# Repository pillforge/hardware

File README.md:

Development Hardware
====================

Schematic and PCB files for development hardware.

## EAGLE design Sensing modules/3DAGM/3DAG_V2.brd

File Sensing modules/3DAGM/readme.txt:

XXXXXXXXXXXXXXXXXXXXXXXXXXXXXXXXXXXXXXXXXXXXXXXXXXXXXXXXXXXXXXXXXXXXXXXXXXXXX
X                                                                           X
X   Artwork and documentation done by: STORM LAB                            X
X                                                                           X
X   Company: VANDERBILT UNIVERSITY                                          X
XXXXXXXXXXXXXXXXXXXXXXXXXXXXXXXXXXXXXXXXXXXXXXXXXXXXXXXXXXXXXXXXXXXXXXXXXXXXX

PROJECT : 3DAGM
PCB NAME : 3DAGM
REVISION: 1.1 
DATE: 4-28-2015

PCB DESCRIPTION: 2 LAYER PCB 0.8 MM NOMINAL THICKNESS FR4
		Dimensions in mil (0.001 inch)
                            DOUBLE SIDE SOLDER MASK,
                            DOUBLE SIDE SILKSCREEN,
                            6 MIL MIN TRACE WIDTH AND 6 MIL MIN ISOLATION
		Dielectric constant for FR4 is 4.5

FILE NAME            		DESCRIPTION                               	FILE TYPE
-------------------------------------------------------------------------------------------
***PCB MANUFACTURING FILES:
3DAGM.cmp				LAYER 1 COMPONENT SIDE/POSITIV              EXT. GERBER
3DAGM.sol				LAYER 2 Inner layer/POSITIV                 EXT. GERBER

3DAGM.stc				SOLDER MASK COMPONENT SIDE/NEGATIVE         EXT. GERBER
3DAGM.stl				SOLDER MASK SOLDER SIDE/NEGATIVE            EXT. GERBER

3DAGM.plc				SILKSCREEN COMPONENT SIDE/POSITIVE          EXT. GERBER
3DAGM.pls				SILKSCREEN SOLDER SIDE/POSITIVE             EXT. GERBER

3DAGM.crc				SOLDER PAST COMPONENT SIDE/POSITIVE         EXT. GERBER
3DAGM.crs				SOLDER PAST SOLDER SIDE/POSITIVE            EXT. GERBER

3DAGM.drd				DRILL/MECHANICAL DRAWING                    EXT. GERBER
3DAGM.dri				DRILL/NC DRILL REPORT                       ASCII
3DAGM.dim				BOARD OUTLINE             		    EXT. GERBER

3DAGM_partlist.xls		PART LIST					    ASCII

***PDF FILES:
3DAGM.PDF	Circuit Diagram

***EAGLE  FILES:
3DAGM.SCH			Eagle 6.6 Schematic file
3DAGM.BRD			Eagle 6.6 Layout file

README.TXT              THIS FILE                                   ASCII

***REVISION HISTORY

none

END.

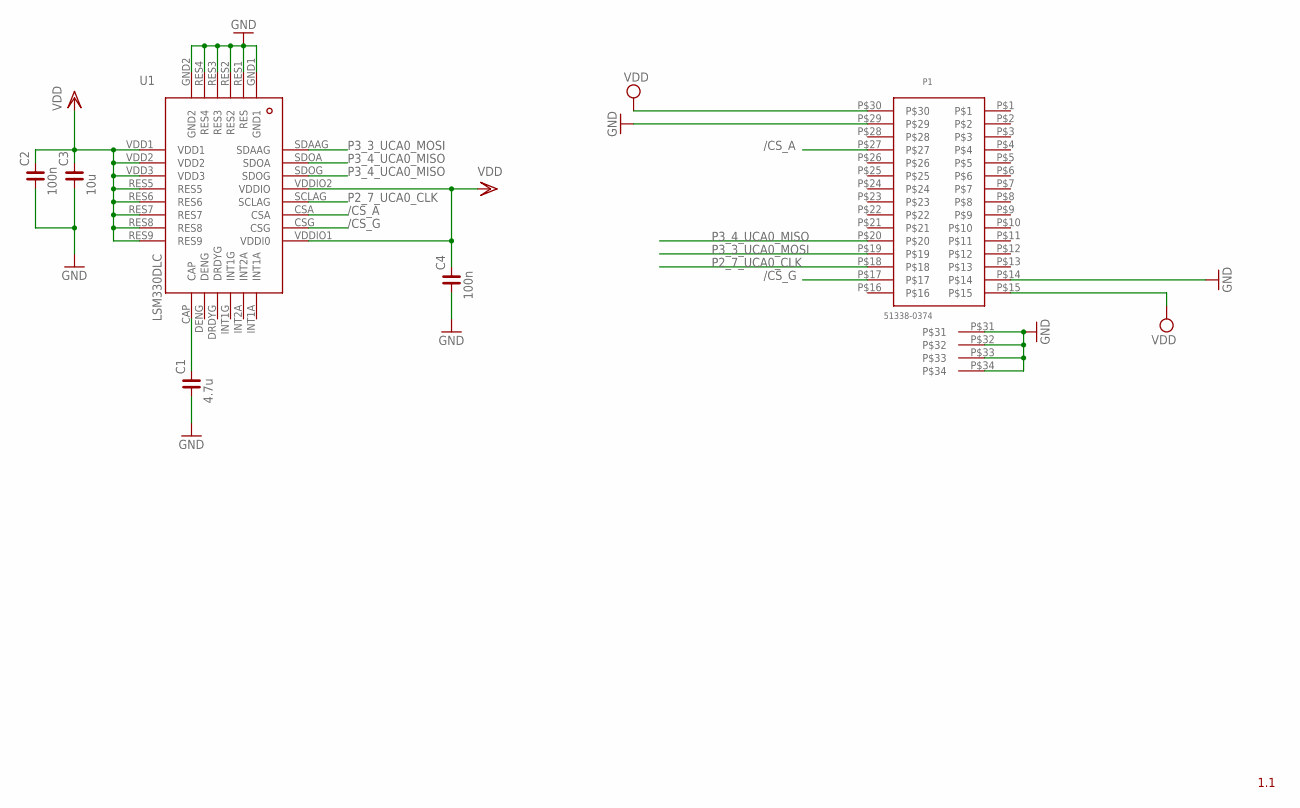
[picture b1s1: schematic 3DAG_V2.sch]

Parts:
C1: 4.7u; C0402
C2, C4: 100n; C0402
C3: 10u; C0402
P1: 51338-0374; 51338-0374_RECEPTACLE
U$4: LSM330DLC

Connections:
/CS_A: P1.P$27, U$4.CSA
/CS_G: P1.P$17, U$4.CSG
GND: C1.1, C2.1, C3.1, C4.1, P1.P$14, P1.P$29, P1.P$31, P1.P$32, P1.P$33, P1.P$34, U$4.GND1, U$4.GND2, U$4.RES1 (RES), U$4.RES2, U$4.RES3, U$4.RES4
unnamed: C1.2, U$4.CAP
P2_7_UCA0_CLK: P1.P$18, U$4.SCLAG
P3_3_UCA0_MOSI: P1.P$19, U$4.SDAAG
P3_4_UCA0_MISO: P1.P$20, U$4.SDOA, U$4.SDOG
VDD: C2.2, C3.2, C4.2, P1.P$15, P1.P$30, U$4.RES5, U$4.RES6, U$4.RES7, U$4.RES8, U$4.RES9, U$4.VDD1, U$4.VDD2, U$4.VDD3, U$4.VDDIO1 (VDDI0), U$4.VDDIO2 (VDDIO)

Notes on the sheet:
1.1

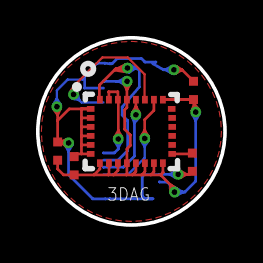
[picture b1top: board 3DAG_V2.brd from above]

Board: 2 copper layers, 10.4 x 10.4 mm, 6 parts (1 on the bottom side), 8 nets.

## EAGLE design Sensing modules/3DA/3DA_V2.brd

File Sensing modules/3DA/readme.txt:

XXXXXXXXXXXXXXXXXXXXXXXXXXXXXXXXXXXXXXXXXXXXXXXXXXXXXXXXXXXXXXXXXXXXXXXXXXXXX
X                                                                           X
X   Artwork and documentation done by: STORM LAB                            X
X                                                                           X
X   Company: VANDERBILT UNIVERSITY                                          X
XXXXXXXXXXXXXXXXXXXXXXXXXXXXXXXXXXXXXXXXXXXXXXXXXXXXXXXXXXXXXXXXXXXXXXXXXXXXX

PROJECT : 3da
PCB NAME : 3da
REVISION: 1.1 
DATE: 4-28-2015

PCB DESCRIPTION: 2 LAYER PCB 0.8 MM NOMINAL THICKNESS FR4
		Dimensions in mil (0.001 inch)
                            DOUBLE SIDE SOLDER MASK,
                            DOUBLE SIDE SILKSCREEN,
                            6 MIL MIN TRACE WIDTH AND 6 MIL MIN ISOLATION
		Dielectric constant for FR4 is 4.5

FILE NAME            		DESCRIPTION                               	FILE TYPE
-------------------------------------------------------------------------------------------
***PCB MANUFACTURING FILES:
3da.cmp				LAYER 1 COMPONENT SIDE/POSITIV              EXT. GERBER
3da.sol				LAYER 2 Inner layer/POSITIV                 EXT. GERBER

3da.stc				SOLDER MASK COMPONENT SIDE/NEGATIVE         EXT. GERBER
3da.stl				SOLDER MASK SOLDER SIDE/NEGATIVE            EXT. GERBER

3da.plc				SILKSCREEN COMPONENT SIDE/POSITIVE          EXT. GERBER
3da.pls				SILKSCREEN SOLDER SIDE/POSITIVE             EXT. GERBER

3da.crc				SOLDER PAST COMPONENT SIDE/POSITIVE         EXT. GERBER
3da.crs				SOLDER PAST SOLDER SIDE/POSITIVE            EXT. GERBER

3da.drd				DRILL/MECHANICAL DRAWING                    EXT. GERBER
3da.dri				DRILL/NC DRILL REPORT                       ASCII

3da_partlist.xls		PART LIST									ASCII

***PDF FILES:
3da.PDF	Circuit Diagram

***EAGLE  FILES:
3da.SCH			Eagle 6.6 Schematic file
3da.BRD			Eagle 6.6 Layout file

README.TXT              THIS FILE                                   ASCII

***REVISION HISTORY

none

END.

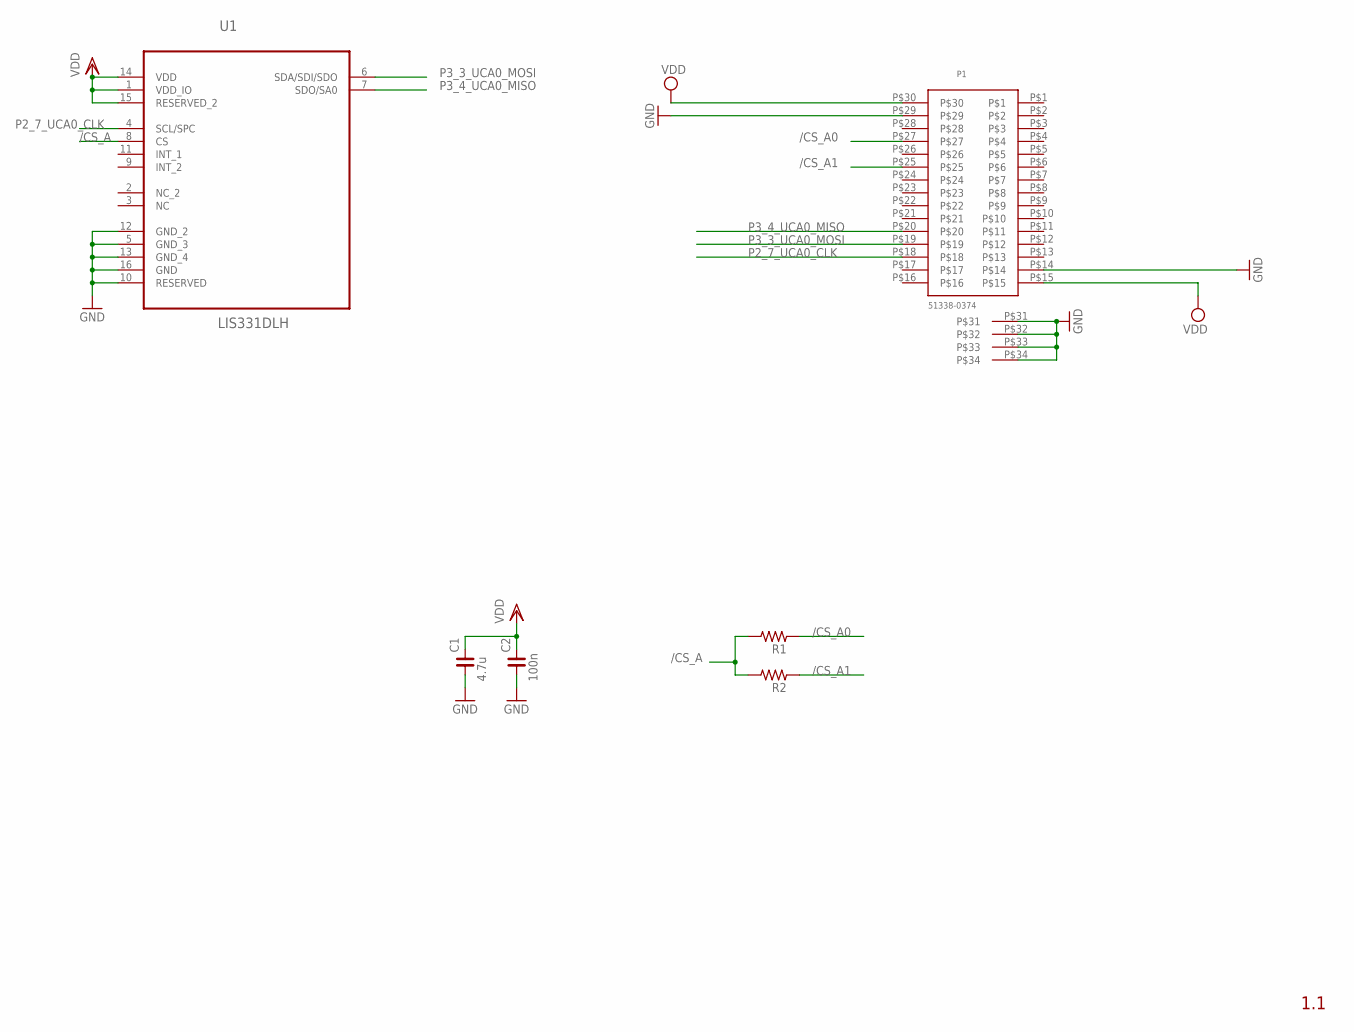
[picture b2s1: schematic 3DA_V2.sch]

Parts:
C1: 4.7u; C0402
C2: 100n; C0402
P1: 51338-0374; 51338-0374_RECEPTACLE
R1, R2: R_0402; R0402
U1: LIS331DLH; LGA16R50P3X5_300X300X100

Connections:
/CS_A: R1.2, R2.2, U1.8 (CS)
/CS_A0: P1.P$27, R1.1
/CS_A1: P1.P$25, R2.1
GND: C1.1, C2.1, P1.P$14, P1.P$29, P1.P$31, P1.P$32, P1.P$33, P1.P$34, U1.5 (GND_3), U1.10 (RESERVED), U1.12 (GND_2), U1.13 (GND_4), U1.16 (GND)
P2_7_UCA0_CLK: P1.P$18, U1.4 (SCL/SPC)
P3_3_UCA0_MOSI: P1.P$19, U1.6 (SDA/SDI/SDO)
P3_4_UCA0_MISO: P1.P$20, U1.7 (SDO/SA0)
VDD: C1.2, C2.2, P1.P$15, P1.P$30, U1.1 (VDD_IO), U1.14 (VDD), U1.15 (RESERVED_2)

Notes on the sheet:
1.1

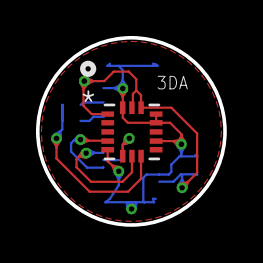
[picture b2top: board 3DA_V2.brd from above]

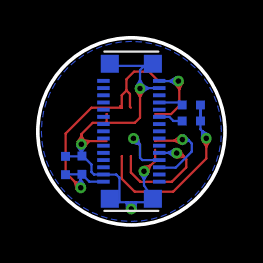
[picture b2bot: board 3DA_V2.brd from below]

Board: 2 copper layers, 10.4 x 10.4 mm, 6 parts (5 on the bottom side), 8 nets.

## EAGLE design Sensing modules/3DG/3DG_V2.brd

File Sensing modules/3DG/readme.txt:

XXXXXXXXXXXXXXXXXXXXXXXXXXXXXXXXXXXXXXXXXXXXXXXXXXXXXXXXXXXXXXXXXXXXXXXXXXXXX
X                                                                           X
X   Artwork and documentation done by: STORM LAB                            X
X                                                                           X
X   Company: VANDERBILT UNIVERSITY                                          X
XXXXXXXXXXXXXXXXXXXXXXXXXXXXXXXXXXXXXXXXXXXXXXXXXXXXXXXXXXXXXXXXXXXXXXXXXXXXX

PROJECT : 3DG
PCB NAME : 3DG
REVISION: 1.1 
DATE: 4-28-2015

PCB DESCRIPTION: 2 LAYER PCB 0.8 MM NOMINAL THICKNESS FR4
		Dimensions in mil (0.001 inch)
                            DOUBLE SIDE SOLDER MASK,
                            DOUBLE SIDE SILKSCREEN,
                            6 MIL MIN TRACE WIDTH AND 6 MIL MIN ISOLATION
		Dielectric constant for FR4 is 4.5

FILE NAME            		DESCRIPTION                               	FILE TYPE
-------------------------------------------------------------------------------------------
***PCB MANUFACTURING FILES:
3DG.cmp				LAYER 1 COMPONENT SIDE/POSITIV              EXT. GERBER
3DG.sol				LAYER 2 Inner layer/POSITIV                 EXT. GERBER

3DG.stc				SOLDER MASK COMPONENT SIDE/NEGATIVE         EXT. GERBER
3DG.stl				SOLDER MASK SOLDER SIDE/NEGATIVE            EXT. GERBER

3DG.plc				SILKSCREEN COMPONENT SIDE/POSITIVE          EXT. GERBER
3DG.pls				SILKSCREEN SOLDER SIDE/POSITIVE             EXT. GERBER

3DG.crc				SOLDER PAST COMPONENT SIDE/POSITIVE         EXT. GERBER
3DG.crs				SOLDER PAST SOLDER SIDE/POSITIVE            EXT. GERBER

3DG.drd				DRILL/MECHANICAL DRAWING                    EXT. GERBER
3DG.dri				DRILL/NC DRILL REPORT                       ASCII
3DG.dim				BOARD OUTLINE             		    EXT. GERBER

3DG_partlist.xls		PART LIST					    ASCII

***PDF FILES:
3DG.PDF	Circuit Diagram

***EAGLE  FILES:
3DG.SCH			Eagle 6.6 Schematic file
3DG.BRD			Eagle 6.6 Layout file

README.TXT              THIS FILE                                   ASCII

***REVISION HISTORY

none

END.

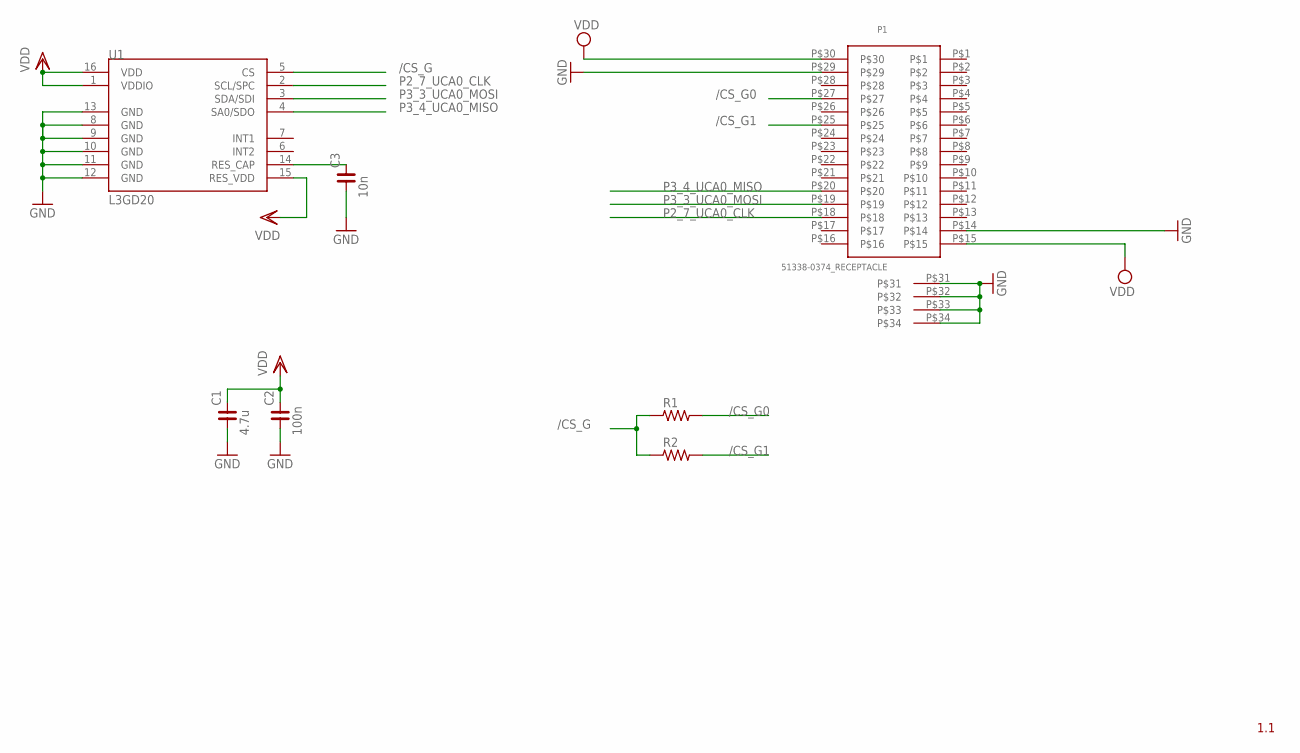
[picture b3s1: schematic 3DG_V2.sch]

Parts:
C1: 4.7u; C0402
C2: 100n; C0402
C3: 10n; C0402
P1: 51338-0374_RECEPTACLE
R1, R2: R_0402; R0402
U1: L3GD20; LGA16-4X4

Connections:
/CS_G: R1.1, R2.1, U1.5 (CS)
/CS_G0: P1.P$27, R1.2
/CS_G1: P1.P$25, R2.2
GND: C1.1, C2.1, C3.1, P1.P$14, P1.P$29, P1.P$31, P1.P$32, P1.P$33, P1.P$34, U1.8 (GND), U1.9 (GND), U1.10 (GND), U1.11 (GND), U1.12 (GND), U1.13 (GND)
unnamed: C3.2, U1.14 (RES_CAP)
P2_7_UCA0_CLK: P1.P$18, U1.2 (SCL/SPC)
P3_3_UCA0_MOSI: P1.P$19, U1.3 (SDA/SDI)
P3_4_UCA0_MISO: P1.P$20, U1.4 (SA0/SDO)
VDD: C1.2, C2.2, P1.P$15, P1.P$30, U1.1 (VDDIO), U1.15 (RES_VDD), U1.16 (VDD)

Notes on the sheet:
1.1

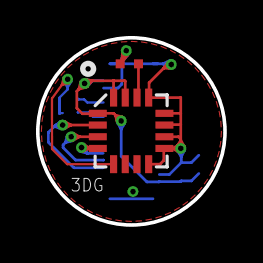
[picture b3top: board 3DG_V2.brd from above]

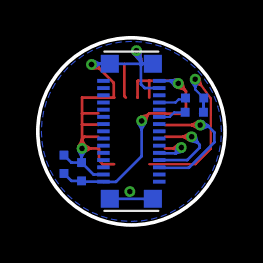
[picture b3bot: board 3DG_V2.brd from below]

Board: 2 copper layers, 10.4 x 10.4 mm, 7 parts (5 on the bottom side), 9 nets.

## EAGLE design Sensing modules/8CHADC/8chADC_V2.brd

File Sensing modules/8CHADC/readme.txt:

XXXXXXXXXXXXXXXXXXXXXXXXXXXXXXXXXXXXXXXXXXXXXXXXXXXXXXXXXXXXXXXXXXXXXXXXXXXXX
X                                                                           X
X   Artwork and documentation done by: STORM LAB                            X
X                                                                           X
X   Company: VANDERBILT UNIVERSITY                                          X
XXXXXXXXXXXXXXXXXXXXXXXXXXXXXXXXXXXXXXXXXXXXXXXXXXXXXXXXXXXXXXXXXXXXXXXXXXXXX

PROJECT : 8chADC
PCB NAME : 8chADC
REVISION: 1.1 
DATE: 4-28-2015

PCB DESCRIPTION: 2 LAYER PCB 0.8 MM NOMINAL THICKNESS FR4
		Dimensions in mil (0.001 inch)
                            DOUBLE SIDE SOLDER MASK,
                            DOUBLE SIDE SILKSCREEN,
                            6 MIL MIN TRACE WIDTH AND 6 MIL MIN ISOLATION
		Dielectric constant for FR4 is 4.5

FILE NAME            		DESCRIPTION                               	FILE TYPE
-------------------------------------------------------------------------------------------
***PCB MANUFACTURING FILES:
8chADC.cmp				LAYER 1 COMPONENT SIDE/POSITIV              EXT. GERBER
8chADC.sol				LAYER 2 Inner layer/POSITIV                 EXT. GERBER

8chADC.stc				SOLDER MASK COMPONENT SIDE/NEGATIVE         EXT. GERBER
8chADC.stl				SOLDER MASK SOLDER SIDE/NEGATIVE            EXT. GERBER

8chADC.plc				SILKSCREEN COMPONENT SIDE/POSITIVE          EXT. GERBER
8chADC.pls				SILKSCREEN SOLDER SIDE/POSITIVE             EXT. GERBER

8chADC.crc				SOLDER PAST COMPONENT SIDE/POSITIVE         EXT. GERBER
8chADC.crs				SOLDER PAST SOLDER SIDE/POSITIVE            EXT. GERBER

8chADC.drd				DRILL/MECHANICAL DRAWING                    EXT. GERBER
8chADC.dri				DRILL/NC DRILL REPORT                       ASCII
8chADC.dim				BOARD OUTLINE             		    EXT. GERBER

8chADC_partlist.xls		PART LIST					    ASCII

***PDF FILES:
8chADC.PDF	Circuit Diagram

***EAGLE  FILES:
8chADC.SCH			Eagle 6.6 Schematic file
8chADC.BRD			Eagle 6.6 Layout file

README.TXT              THIS FILE                                   ASCII

***REVISION HISTORY

none

END.

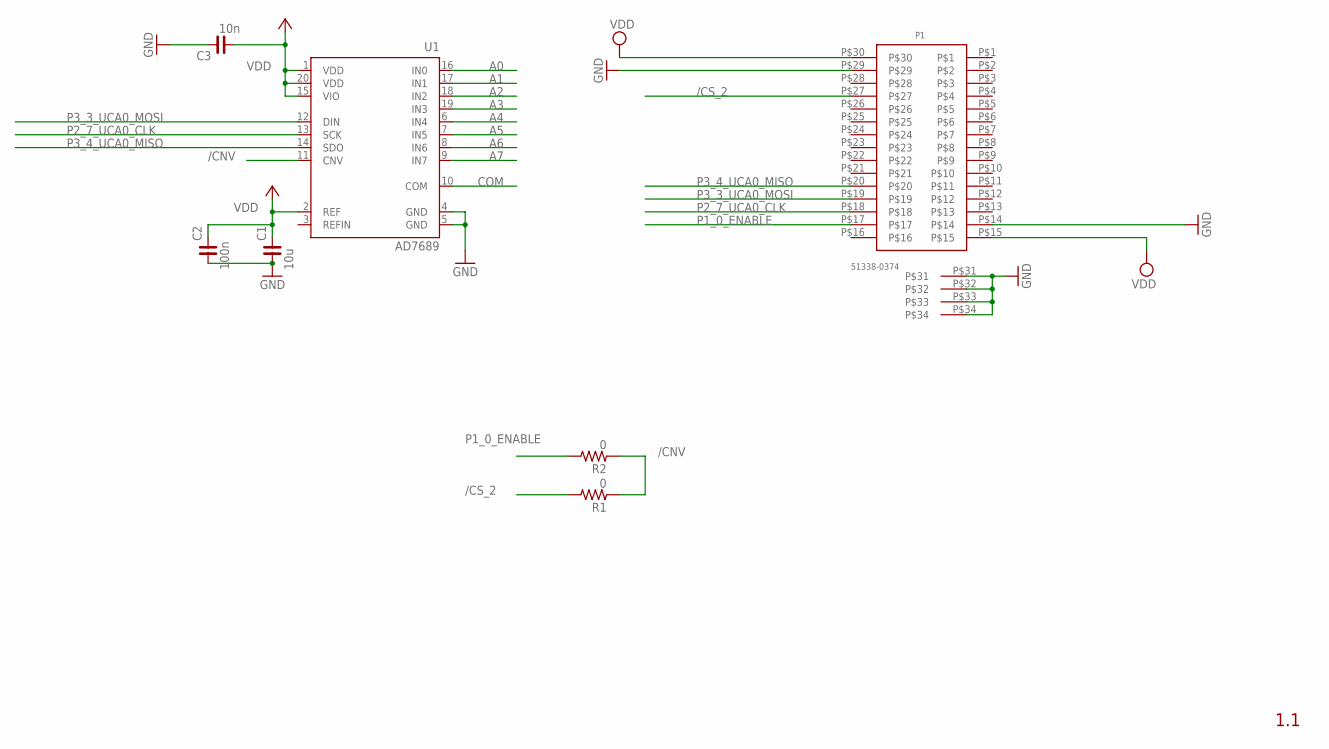
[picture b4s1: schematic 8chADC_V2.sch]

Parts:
C1: 10u; C0402
C2: 100n; C0402
C3: 10n; C0402
P1: 51338-0374; 51338-0374_RECEPTACLE
R1, R2: 0; R0402
U1: AD7689; LFCSP20

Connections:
/CNV: R1.1, R2.1, U1.11 (CNV)
/CS_2: P1.P$27, R1.2
A0: U1.16 (IN0)
A1: U1.17 (IN1)
A2: U1.18 (IN2)
A3: U1.19 (IN3)
A4: U1.6 (IN4)
A5: U1.7 (IN5)
A6: U1.8 (IN6)
A7: U1.9 (IN7)
COM: U1.10 (COM)
GND: C1.1, C2.1, C3.2, P1.P$14, P1.P$29, P1.P$31, P1.P$32, P1.P$33, P1.P$34, U1.4 (GND), U1.5 (GND)
P1_0_ENABLE: P1.P$17, R2.2
P2_7_UCA0_CLK: P1.P$18, U1.13 (SCK)
P3_3_UCA0_MOSI: P1.P$19, U1.12 (DIN)
P3_4_UCA0_MISO: P1.P$20, U1.14 (SDO)
VDD: C1.2, C2.2, C3.1, P1.P$15, P1.P$30, U1.1 (VDD), U1.2 (REF), U1.15 (VIO), U1.20 (VDD)

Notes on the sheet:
1.1

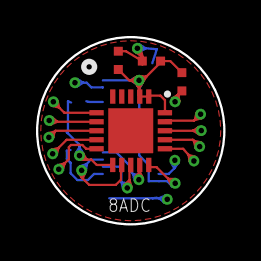
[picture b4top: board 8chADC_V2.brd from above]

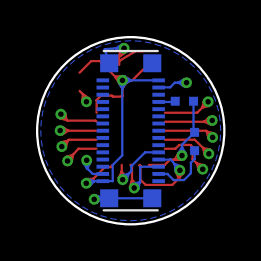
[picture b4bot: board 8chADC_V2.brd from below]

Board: 2 copper layers, 10.4 x 10.4 mm, 7 parts (3 on the bottom side), 8 nets.

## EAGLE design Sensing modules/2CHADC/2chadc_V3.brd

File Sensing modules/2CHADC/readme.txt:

XXXXXXXXXXXXXXXXXXXXXXXXXXXXXXXXXXXXXXXXXXXXXXXXXXXXXXXXXXXXXXXXXXXXXXXXXXXXX
X                                                                           X
X   Artwork and documentation done by: STORM LAB                            X
X                                                                           X
X   Company: VANDERBILT UNIVERSITY                                          X
XXXXXXXXXXXXXXXXXXXXXXXXXXXXXXXXXXXXXXXXXXXXXXXXXXXXXXXXXXXXXXXXXXXXXXXXXXXXX

PROJECT : 2chadc
PCB NAME : 2chadc
REVISION: 1.1 
DATE: 4-28-2015

PCB DESCRIPTION: 2 LAYER PCB 0.8 MM NOMINAL THICKNESS FR4
		Dimensions in mil (0.001 inch)
                            DOUBLE SIDE SOLDER MASK,
                            DOUBLE SIDE SILKSCREEN,
                            6 MIL MIN TRACE WIDTH AND 6 MIL MIN ISOLATION
		Dielectric constant for FR4 is 4.5

FILE NAME            		DESCRIPTION                               	FILE TYPE
-------------------------------------------------------------------------------------------
***PCB MANUFACTURING FILES:
2chadc.cmp				LAYER 1 COMPONENT SIDE/POSITIV              EXT. GERBER
2chadc.sol				LAYER 2 Inner layer/POSITIV                 EXT. GERBER

2chadc.stc				SOLDER MASK COMPONENT SIDE/NEGATIVE         EXT. GERBER
2chadc.stl				SOLDER MASK SOLDER SIDE/NEGATIVE            EXT. GERBER

2chadc.plc				SILKSCREEN COMPONENT SIDE/POSITIVE          EXT. GERBER
2chadc.pls				SILKSCREEN SOLDER SIDE/POSITIVE             EXT. GERBER

2chadc.crc				SOLDER PAST COMPONENT SIDE/POSITIVE         EXT. GERBER
2chadc.crs				SOLDER PAST SOLDER SIDE/POSITIVE            EXT. GERBER

2chadc.drd				DRILL/MECHANICAL DRAWING                    EXT. GERBER
2chadc.dri				DRILL/NC DRILL REPORT                       ASCII

2chadc.dim				BOARD OUTLINE                      			EXT. GERBER

2chadc_partlist.xls		PART LIST									ASCII

***PDF FILES:
2chadc.PDF	Circuit Diagram

***EAGLE  FILES:
2chadc.SCH			Eagle 6.6 Schematic file
2chadc.BRD			Eagle 6.6 Layout file

README.TXT              THIS FILE                                   ASCII

***REVISION HISTORY

none

END.

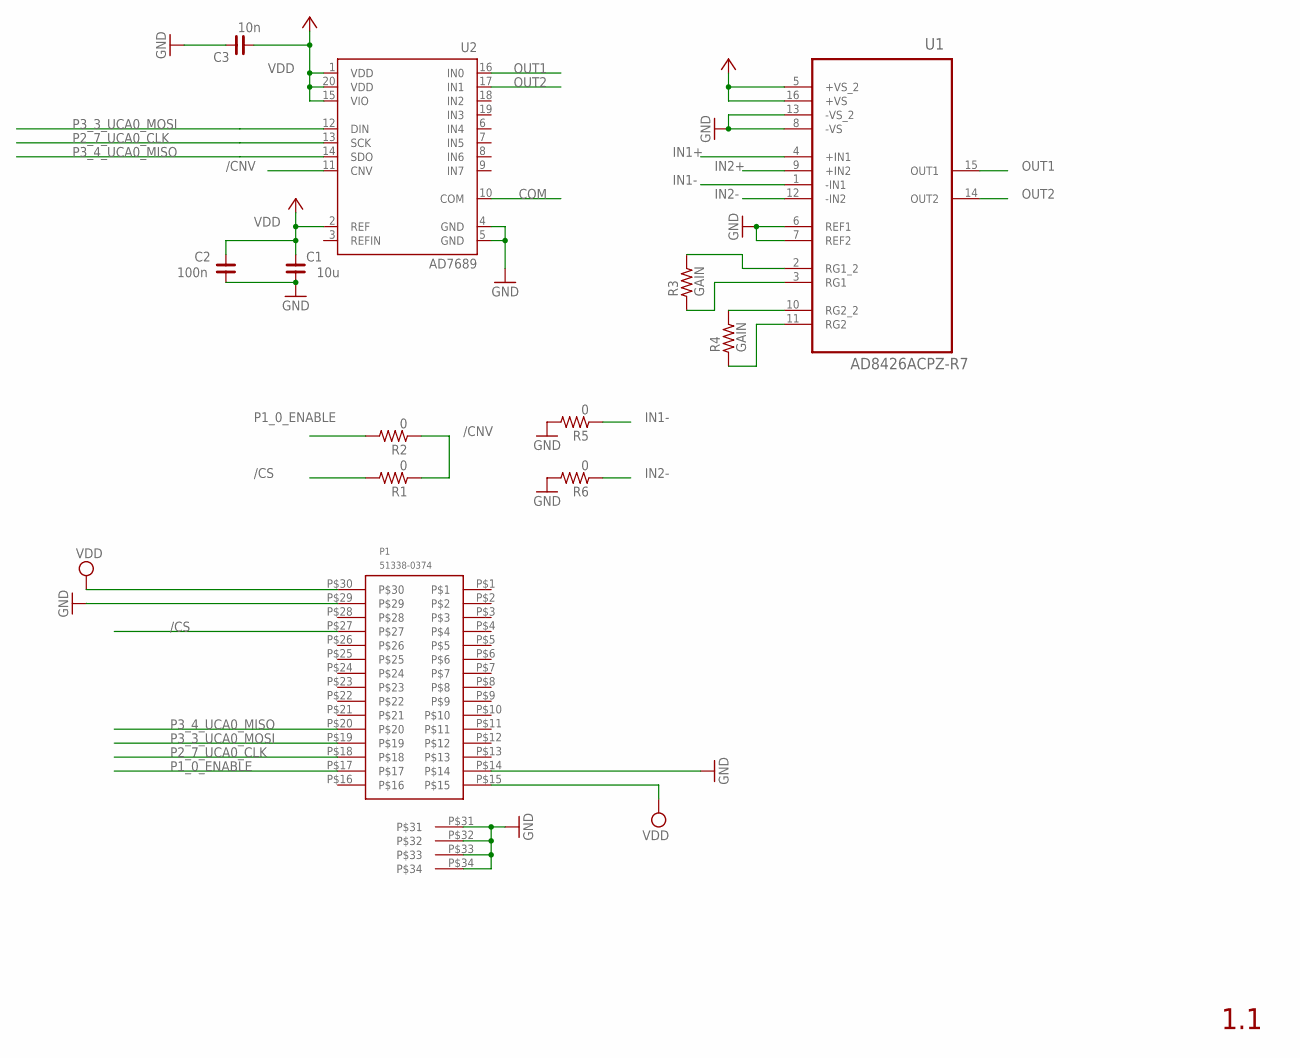
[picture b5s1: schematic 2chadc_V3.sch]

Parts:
C1: 10u; C0402
C2: 100n; C0402
C3: 10n; C0402
P1: 51338-0374; 51338-0374_RECEPTACLE
R1, R2, R5, R6: 0; R0402
R3, R4: GAIN; R0402
U1: AD8426ACPZ-R7; QFN65P400X400X100-16N
U2: AD7689; LFCSP20

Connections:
+3V3: U1.5 (+VS_2), U1.16 (+VS)
/CNV: R1.1, R2.1, U2.11 (CNV)
/CS: P1.P$27, R1.2
COM: U2.10 (COM)
GND: C1.1, C2.1, C3.2, P1.P$14, P1.P$29, P1.P$31, P1.P$32, P1.P$33, P1.P$34, R5.2, R6.2, U1.6 (REF1), U1.7 (REF2), U1.8 (-VS), U1.13 (-VS_2), U2.4 (GND), U2.5 (GND)
IN1+: U1.4 (+IN1)
IN1-: R5.1, U1.1 (-IN1)
IN2+: U1.9 (+IN2)
IN2-: R6.1, U1.12 (-IN2)
unnamed: R4.2, U1.10 (RG2_2)
unnamed: R4.1, U1.11 (RG2)
unnamed: R3.1, U1.3 (RG1)
unnamed: R3.2, U1.2 (RG1_2)
OUT1: U1.15 (OUT1), U2.16 (IN0)
OUT2: U1.14 (OUT2), U2.17 (IN1)
P1_0_ENABLE: P1.P$17, R2.2
P2_7_UCA0_CLK: P1.P$18, U2.13 (SCK)
P3_3_UCA0_MOSI: P1.P$19, U2.12 (DIN)
P3_4_UCA0_MISO: P1.P$20, U2.14 (SDO)
VDD: C1.2, C2.2, C3.1, P1.P$15, P1.P$30, U2.1 (VDD), U2.2 (REF), U2.15 (VIO), U2.20 (VDD)

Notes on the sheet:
1.1

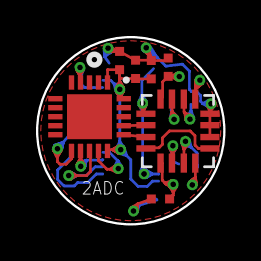
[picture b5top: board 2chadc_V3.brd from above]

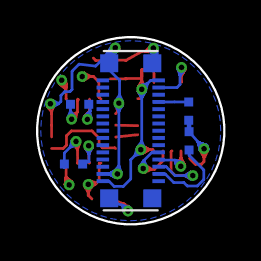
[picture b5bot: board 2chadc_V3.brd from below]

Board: 2 copper layers, 10.4 x 10.4 mm, 12 parts (5 on the bottom side), 17 nets.

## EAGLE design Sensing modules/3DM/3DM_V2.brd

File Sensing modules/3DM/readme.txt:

XXXXXXXXXXXXXXXXXXXXXXXXXXXXXXXXXXXXXXXXXXXXXXXXXXXXXXXXXXXXXXXXXXXXXXXXXXXXX
X                                                                           X
X   Artwork and documentation done by: STORM LAB                            X
X                                                                           X
X   Company: VANDERBILT UNIVERSITY                                          X
XXXXXXXXXXXXXXXXXXXXXXXXXXXXXXXXXXXXXXXXXXXXXXXXXXXXXXXXXXXXXXXXXXXXXXXXXXXXX

PROJECT : 3DM
PCB NAME : 3DM
REVISION: 1.1 
DATE: 4-28-2015

PCB DESCRIPTION: 2 LAYER PCB 0.8 MM NOMINAL THICKNESS FR4
		Dimensions in mil (0.001 inch)
                            DOUBLE SIDE SOLDER MASK,
                            DOUBLE SIDE SILKSCREEN,
                            6 MIL MIN TRACE WIDTH AND 6 MIL MIN ISOLATION
		Dielectric constant for FR4 is 4.5

FILE NAME            		DESCRIPTION                               	FILE TYPE
-------------------------------------------------------------------------------------------
***PCB MANUFACTURING FILES:
3DM.cmp				LAYER 1 COMPONENT SIDE/POSITIV              EXT. GERBER
3DM.sol				LAYER 2 Inner layer/POSITIV                 EXT. GERBER

3DM.stc				SOLDER MASK COMPONENT SIDE/NEGATIVE         EXT. GERBER
3DM.stl				SOLDER MASK SOLDER SIDE/NEGATIVE            EXT. GERBER

3DM.plc				SILKSCREEN COMPONENT SIDE/POSITIVE          EXT. GERBER
3DM.pls				SILKSCREEN SOLDER SIDE/POSITIVE             EXT. GERBER

3DM.crc				SOLDER PAST COMPONENT SIDE/POSITIVE         EXT. GERBER
3DM.crs				SOLDER PAST SOLDER SIDE/POSITIVE            EXT. GERBER

3DM.drd				DRILL/MECHANICAL DRAWING                    EXT. GERBER
3DM.dri				DRILL/NC DRILL REPORT                       ASCII
3DM.dim				BOARD OUTLINE             		    EXT. GERBER

3DM_partlist.xls		PART LIST					    ASCII

***PDF FILES:
3DM.PDF	Circuit Diagram

***EAGLE  FILES:
3DM.SCH			Eagle 6.6 Schematic file
3DM.BRD			Eagle 6.6 Layout file

README.TXT              THIS FILE                                   ASCII

***REVISION HISTORY

none

END.

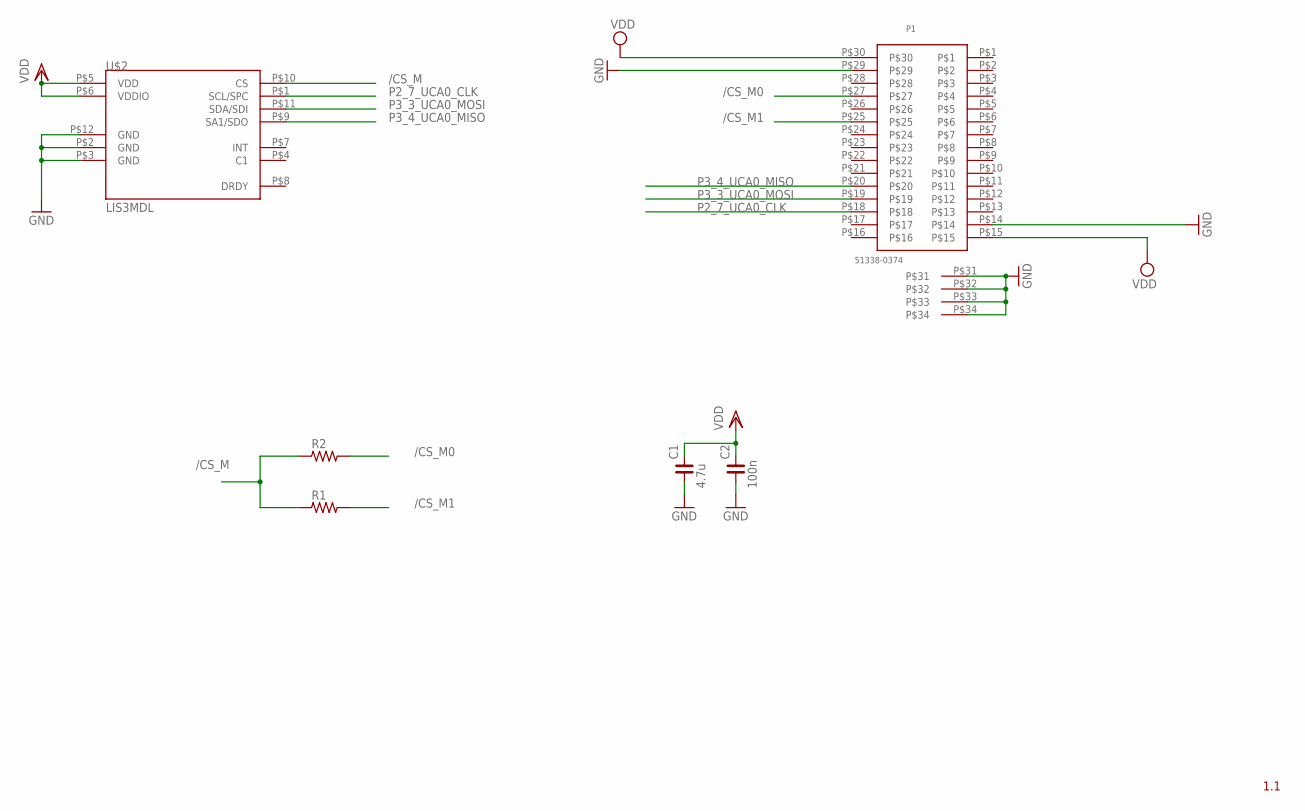
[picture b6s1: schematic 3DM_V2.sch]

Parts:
C1: 4.7u; C0402
C2: 100n; C0402
P1: 51338-0374; 51338-0374_RECEPTACLE
R1, R2: R_0402; R0402
U$2: LIS3MDL; VFLGA-2X2X1

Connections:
/CS_M: R1.1, R2.1, U$2.P$10 (CS)
/CS_M0: P1.P$27, R2.2
/CS_M1: P1.P$25, R1.2
GND: C1.1, C2.1, P1.P$14, P1.P$29, P1.P$31, P1.P$32, P1.P$33, P1.P$34, U$2.P$2 (GND), U$2.P$3 (GND), U$2.P$12 (GND)
P2_7_UCA0_CLK: P1.P$18, U$2.P$1 (SCL/SPC)
P3_3_UCA0_MOSI: P1.P$19, U$2.P$11 (SDA/SDI)
P3_4_UCA0_MISO: P1.P$20, U$2.P$9 (SA1/SDO)
VDD: C1.2, C2.2, P1.P$15, P1.P$30, U$2.P$5 (VDD), U$2.P$6 (VDDIO)

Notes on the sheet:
1.1

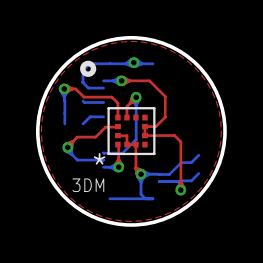
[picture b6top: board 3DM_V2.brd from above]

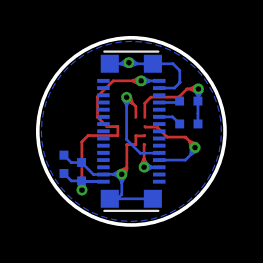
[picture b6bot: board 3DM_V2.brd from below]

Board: 2 copper layers, 10.4 x 10.4 mm, 6 parts (5 on the bottom side), 8 nets.

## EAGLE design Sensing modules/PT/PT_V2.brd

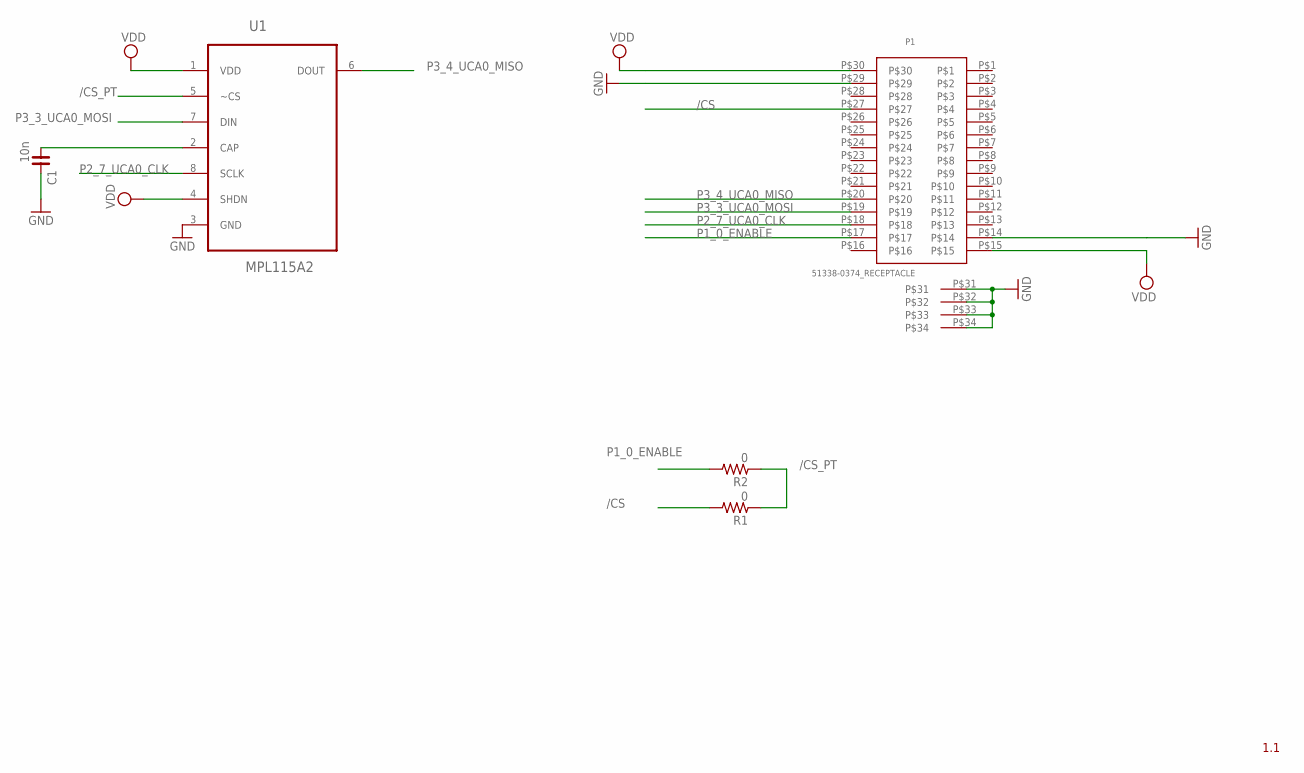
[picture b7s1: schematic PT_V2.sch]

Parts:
C1: 10n; C0402
P1: 51338-0374_RECEPTACLE
R1, R2: 0; R0402
U1: MPL115A2; LGA8R125P0X4_500X300X120

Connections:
/CS: P1.P$27, R1.2
/CS_PT: R1.1, R2.1, U1.5 (~CS)
GND: C1.2, P1.P$14, P1.P$29, P1.P$31, P1.P$32, P1.P$33, P1.P$34, U1.3 (GND)
unnamed: C1.1, U1.2 (CAP)
P1_0_ENABLE: P1.P$17, R2.2
P2_7_UCA0_CLK: P1.P$18, U1.8 (SCLK)
P3_3_UCA0_MOSI: P1.P$19, U1.7 (DIN)
P3_4_UCA0_MISO: P1.P$20, U1.6 (DOUT)
VDD: P1.P$15, P1.P$30, U1.1 (VDD), U1.4 (SHDN)

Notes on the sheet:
1.1

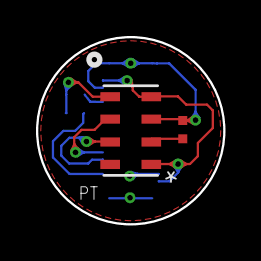
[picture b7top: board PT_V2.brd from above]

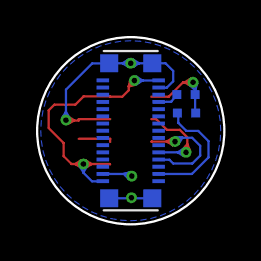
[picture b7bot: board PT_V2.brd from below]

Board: 2 copper layers, 10.4 x 10.4 mm, 5 parts (3 on the bottom side), 9 nets.

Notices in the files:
parts and their libraries:
rc-master-smd: Copyright (C) 2007, Bob Starr
SparkFun-Sensors: Licensing: Creative Commons ShareAlike 4.0 International - https://creativecommons.org/licenses/by-sa/4.0
